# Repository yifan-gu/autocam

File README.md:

Arduino files for my auto-following camera car!

## TODO
- [x] Add dji remote control and receiver
- [x] <s>Add PID encoder</s> Add a web page for parameters
- [x] Add BLE central for the anchor
- [x] Read joystick values for the remote controller
- [x] Read mode switch button for remote controller
- [x] Add state indicator in the web UI
- [x] Add LED state indicators
- [x] Add battery state LED (tag, remote)
- [x] Add LED logic for tag
- [x] Add lock mode (remote)
- [x] Combine tag and remote
  - [x] Add tag selector (sensor, remote)
- [x] Control the BLE data rate
- [x] Fix UWB Anchor naming, fix AutocamController naming
- [x] Add PCB boards
  - [x] Sensor
  - [x] Verify LED resistor values
  - [x] Verify IO0/IO1 port on the ESP32 UWB is usable 
  - [x] Tag
  - [x] Server
  - [x] Remote
- [x] Smooth the distance measurement.
- [x] Added a different mode (follow).
- [x] Added gimbal recenter and camera recording.
- [x] Assemble together
- [x] Design and make the enclosure
- [ ] Calibrate the UWB tag and anchor
- [ ] Measure battery voltage.
- [ ] (optimize) Store settings in external storage (SD card)
- [x] (optimize) Refactor the server code with a state machine, (Almost a state machine now).
- [ ] (optimize) Refactor the sensor LED control with LED controller
- [ ] (optimize) Reorganize shared code into libraries, add external dependencies 

- [x] heartbeat for the remote controller.
- [ ] <s> Nice to have, detect active track failure</s> Turns out there's no API support for that
- [x] Smart Phone APP for the remote (BLE version).

## KNOWN ISSUES
- [ ] Webserver stabability.
- [x] Steering thread issue (Do not steer before throttle is applied)
- [x] BLE connection issue
- [ ] ESC init issue

<s>- [x] Start/stop recording issue</s> Not actually an issue—I plugged the USB-C cable into the wrong gimbal port. However, since the camera drains the gimbal’s battery, I still remove the cable to conserve power.

- [x] Every time the remote buttons are pressed, send values to the server.

## 🚗 Simulator

👉 [Run the Simulator](https://yifan-gu.github.io/autocam/simulator.html)

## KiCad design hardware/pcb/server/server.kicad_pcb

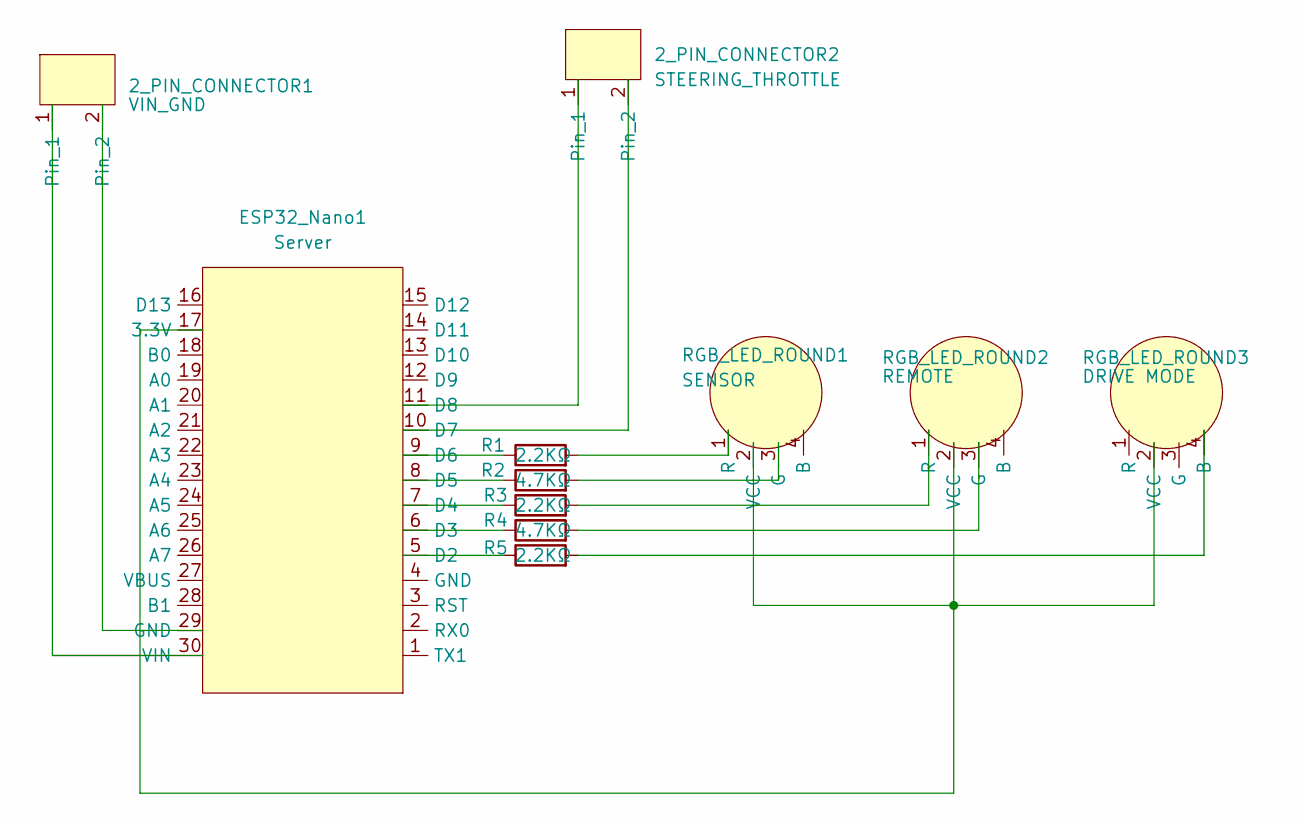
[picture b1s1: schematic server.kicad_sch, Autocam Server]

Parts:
2_PIN_CONNECTOR1: VIN_GND; 2-PIN Connector
2_PIN_CONNECTOR2: STEERING_THROTTLE; 2-PIN Connector
ESP32_Nano1: Server; Arduino ESP32 Nano
R1, R3, R5: 2.2KΩ; Simple Resistor
R2, R4: 4.7KΩ; Simple Resistor
RGB_LED_ROUND1: SENSOR; Anode RGB LED (Round)
RGB_LED_ROUND2: REMOTE; Anode RGB LED (Round)
RGB_LED_ROUND3: DRIVE MODE; Anode RGB LED (Round)

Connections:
unnamed: 2_PIN_CONNECTOR1.1, ESP32_Nano1.30 (VIN)
unnamed: 2_PIN_CONNECTOR1.2, ESP32_Nano1.29 (GND)
unnamed: 2_PIN_CONNECTOR2.1, ESP32_Nano1.11 (D8)
unnamed: 2_PIN_CONNECTOR2.2, ESP32_Nano1.10 (D7)
unnamed: ESP32_Nano1.17 (3.3V), RGB_LED_ROUND1.2 (VCC), RGB_LED_ROUND2.2 (VCC), RGB_LED_ROUND3.2 (VCC)
unnamed: ESP32_Nano1.5 (D2), R5.1
unnamed: ESP32_Nano1.6 (D3), R4.1
unnamed: ESP32_Nano1.7 (D4), R3.1
unnamed: ESP32_Nano1.8 (D5), R2.1
unnamed: ESP32_Nano1.9 (D6), R1.1
unnamed: R2.2, RGB_LED_ROUND1.3 (G)
unnamed: R1.2, RGB_LED_ROUND1.1 (R)
unnamed: R4.2, RGB_LED_ROUND2.3 (G)
unnamed: R3.2, RGB_LED_ROUND2.1 (R)
unnamed: R5.2, RGB_LED_ROUND3.4 (B)

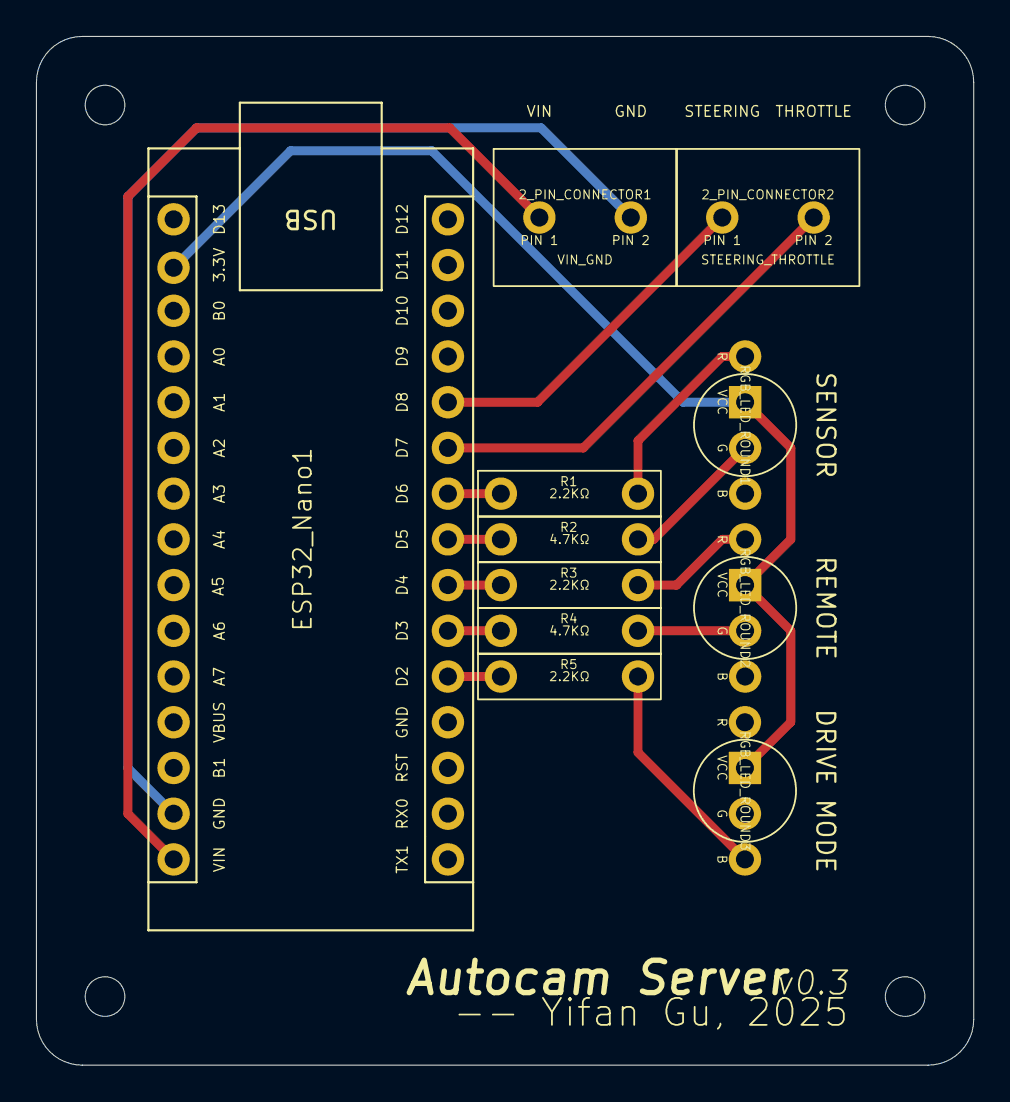
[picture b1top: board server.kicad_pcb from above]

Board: 2 copper layers, 52.1 x 57.2 mm, 11 parts (0 on the bottom side), 15 nets.

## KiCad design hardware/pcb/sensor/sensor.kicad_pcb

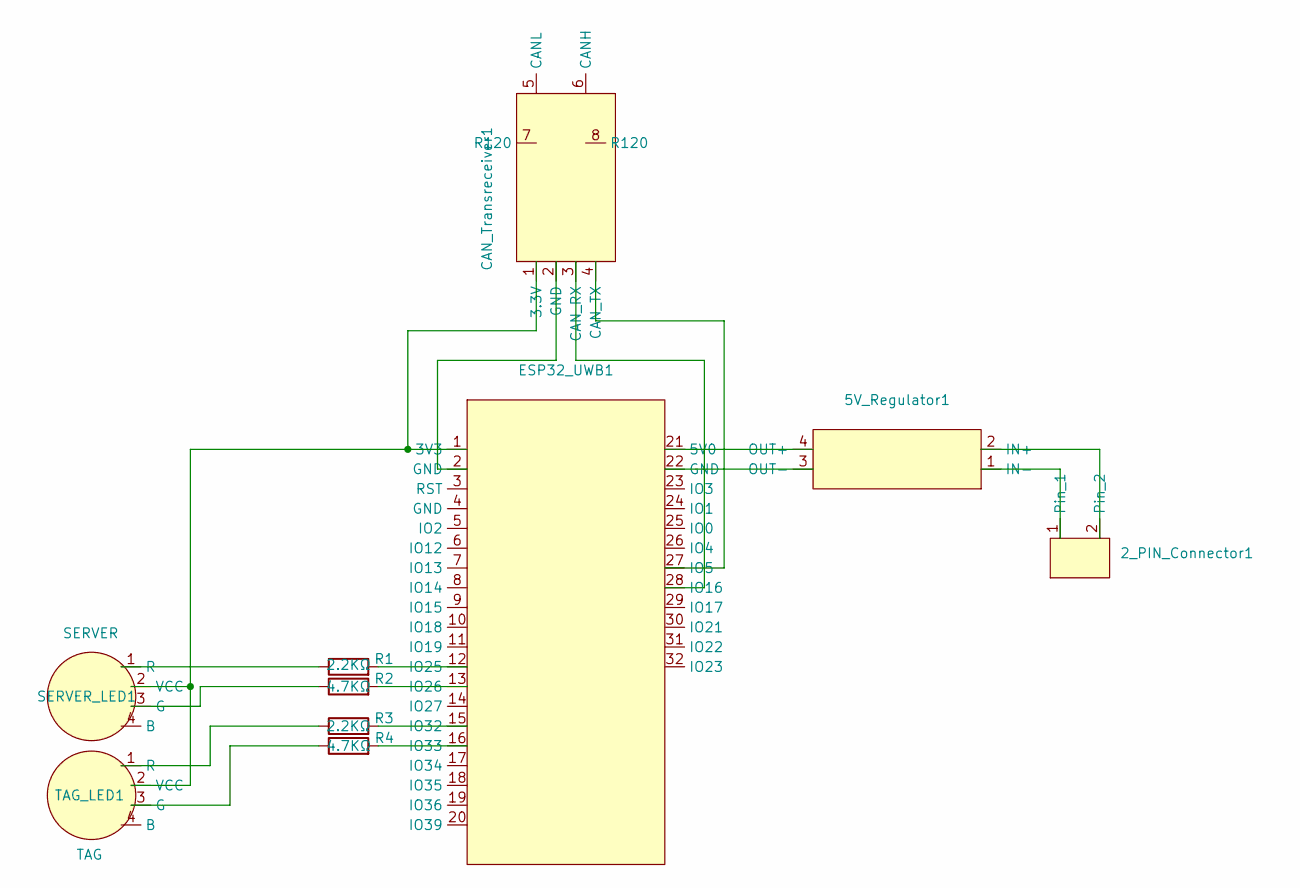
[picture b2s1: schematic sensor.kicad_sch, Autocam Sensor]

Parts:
2_PIN_Connector1: 2-PIN Connector
5V_Regulator1: MP1584EN 5V Regulator
CAN_Transreceiver1: Waveshare CAN Transreceiver
ESP32_UWB1: Makersfab ESP32 UWB
R1, R3: 2.2KΩ; Simple Resistor
R2, R4: 4.7KΩ; Simple Resistor
SERVER_LED1: SERVER; Anode RGB LED (Round)
TAG_LED1: TAG; Anode RGB LED (Round)

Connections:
unnamed: 2_PIN_Connector1.1, 5V_Regulator1.1 (IN-)
unnamed: 2_PIN_Connector1.2, 5V_Regulator1.2 (IN+)
unnamed: 5V_Regulator1.4 (OUT+), ESP32_UWB1.21 (5V0)
unnamed: 5V_Regulator1.3 (OUT-), ESP32_UWB1.22 (GND)
unnamed: CAN_Transreceiver1.1 (3.3V), ESP32_UWB1.1 (3V3), SERVER_LED1.2 (VCC), TAG_LED1.2 (VCC)
unnamed: CAN_Transreceiver1.3 (CAN_RX), ESP32_UWB1.28 (IO16)
unnamed: CAN_Transreceiver1.4 (CAN_TX), ESP32_UWB1.27 (IO5)
unnamed: CAN_Transreceiver1.2 (GND), ESP32_UWB1.2 (GND)
unnamed: ESP32_UWB1.12 (IO25), R1.2
unnamed: ESP32_UWB1.13 (IO26), R2.2
unnamed: ESP32_UWB1.15 (IO32), R3.2
unnamed: ESP32_UWB1.16 (IO33), R4.2
unnamed: R2.1, SERVER_LED1.3 (G)
unnamed: R1.1, SERVER_LED1.1 (R)
unnamed: R4.1, TAG_LED1.3 (G)
unnamed: R3.1, TAG_LED1.1 (R)

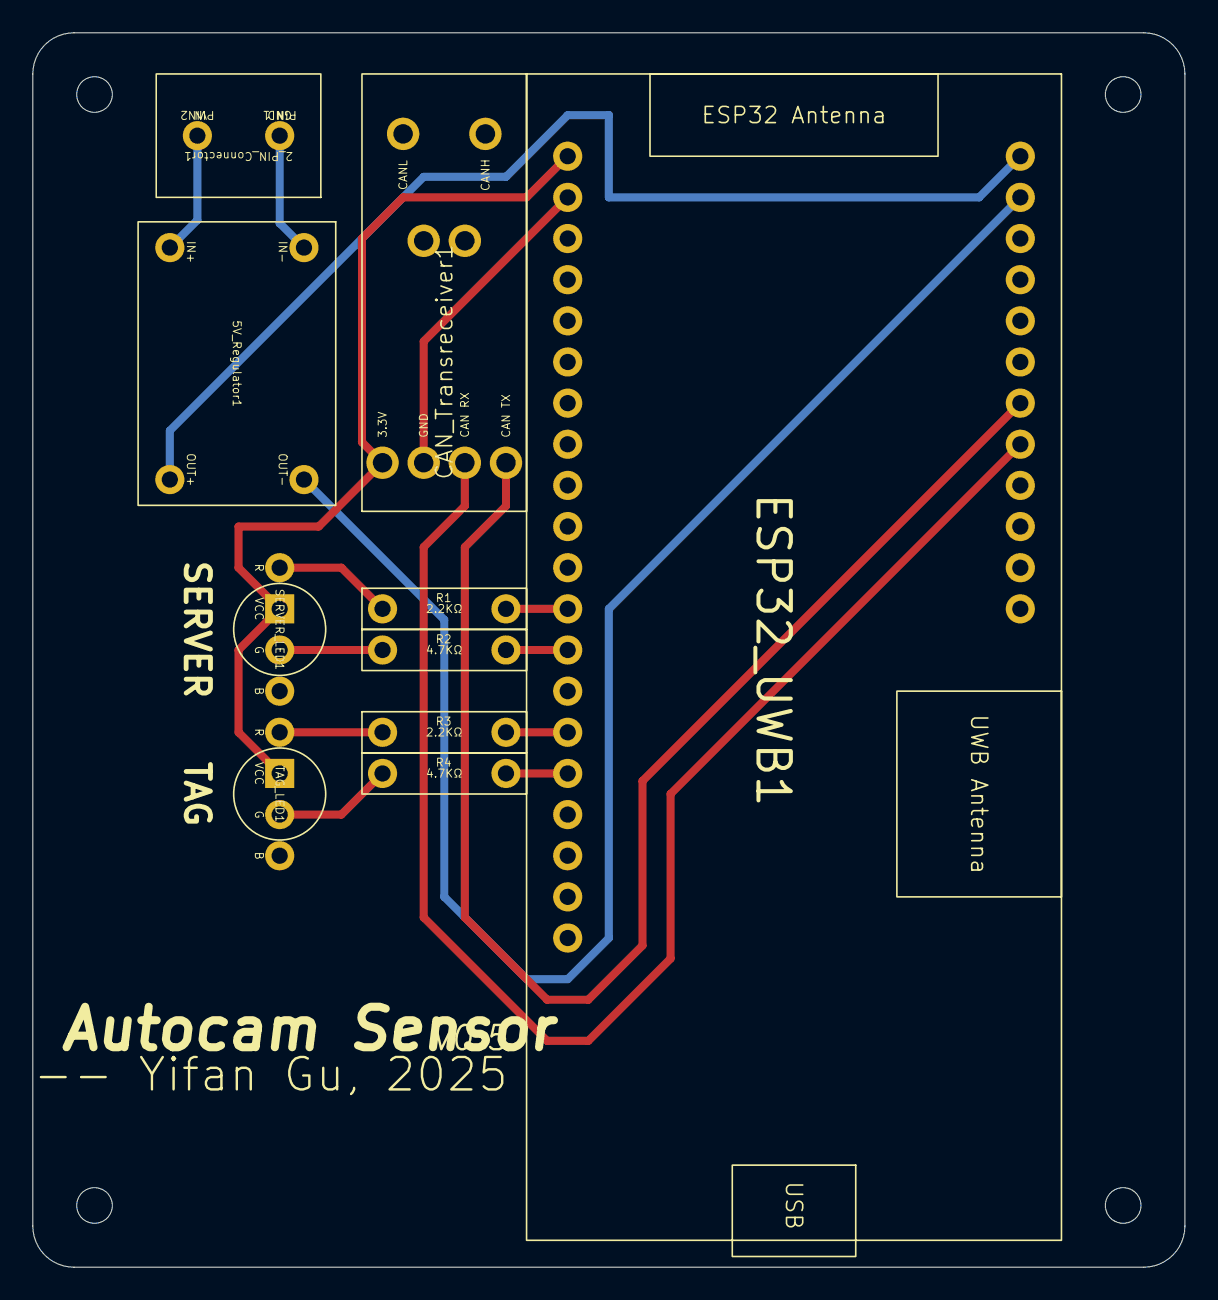
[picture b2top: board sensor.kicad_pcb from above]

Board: 2 copper layers, 71.1 x 76.2 mm, 10 parts (0 on the bottom side), 16 nets.

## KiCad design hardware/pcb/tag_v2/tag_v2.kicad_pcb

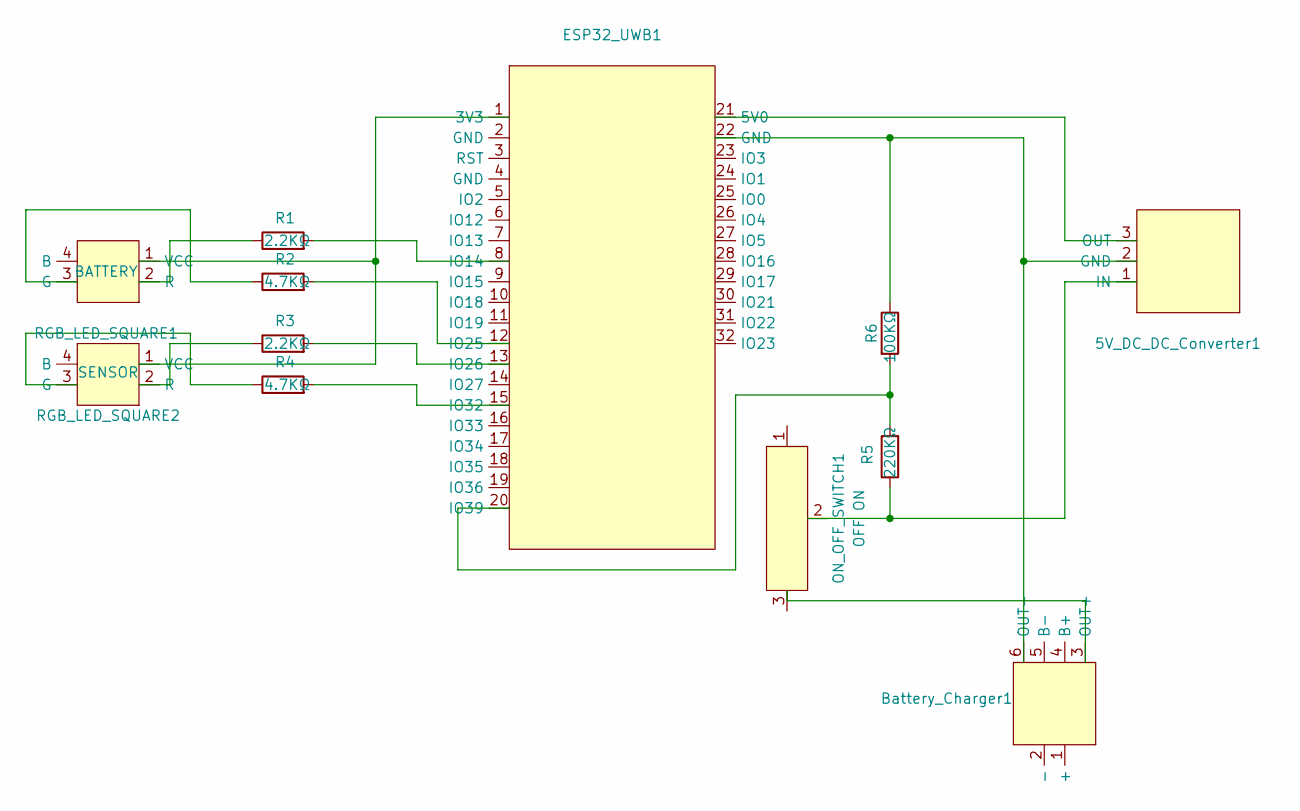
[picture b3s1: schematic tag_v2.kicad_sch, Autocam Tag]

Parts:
5V_DC_DC_Converter1: 5V DC-DC Step Up Converter (Square)
Battery_Charger1: USB-C 3.7V Lithium Battery Charger
ESP32_UWB1: Makersfab ESP32 UWB
ON_OFF_SWITCH1: OFF ON; 3-PIN Switch
R1, R3: 2.2KΩ; Simple Resistor
R2, R4: 4.7KΩ; Simple Resistor
R5: 220KΩ; Simple Resistor
R6: 100KΩ; Simple Resistor
RGB_LED_SQUARE1: BATTERY; Anode RGB LED (Square)
RGB_LED_SQUARE2: SENSOR; Anode RGB LED (Square)

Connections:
unnamed: 5V_DC_DC_Converter1.2 (GND), Battery_Charger1.6 (OUT-), ESP32_UWB1.22 (GND), R6.1
unnamed: 5V_DC_DC_Converter1.1 (IN), ON_OFF_SWITCH1.2, R5.1
unnamed: 5V_DC_DC_Converter1.3 (OUT), ESP32_UWB1.21 (5V0)
unnamed: Battery_Charger1.3 (OUT+), ON_OFF_SWITCH1.3
unnamed: ESP32_UWB1.1 (3V3), RGB_LED_SQUARE1.1 (VCC), RGB_LED_SQUARE2.1 (VCC)
unnamed: ESP32_UWB1.8 (IO14), R1.2
unnamed: ESP32_UWB1.12 (IO25), R2.2
unnamed: ESP32_UWB1.13 (IO26), R3.2
unnamed: ESP32_UWB1.15 (IO32), R4.2
unnamed: ESP32_UWB1.20 (IO39), R5.2, R6.2
unnamed: R2.1, RGB_LED_SQUARE1.3 (G)
unnamed: R1.1, RGB_LED_SQUARE1.2 (R)
unnamed: R4.1, RGB_LED_SQUARE2.3 (G)
unnamed: R3.1, RGB_LED_SQUARE2.2 (R)

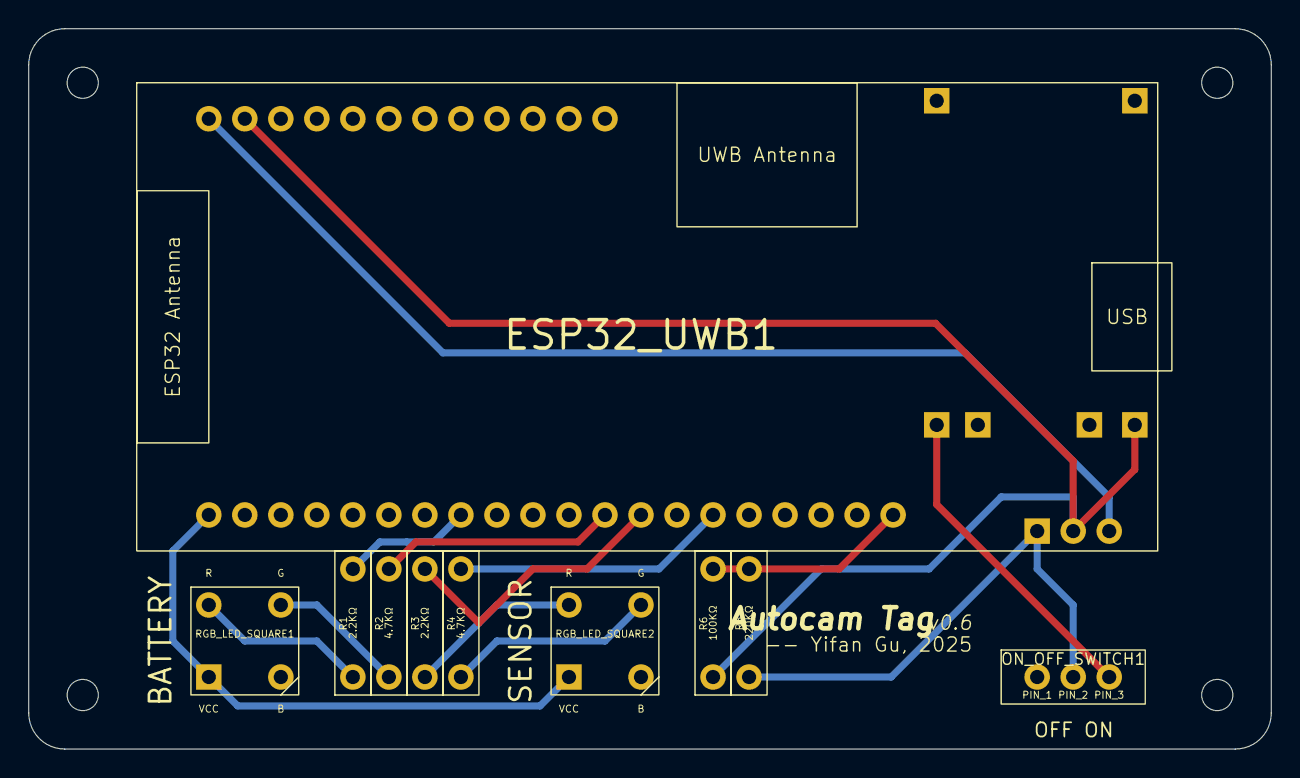
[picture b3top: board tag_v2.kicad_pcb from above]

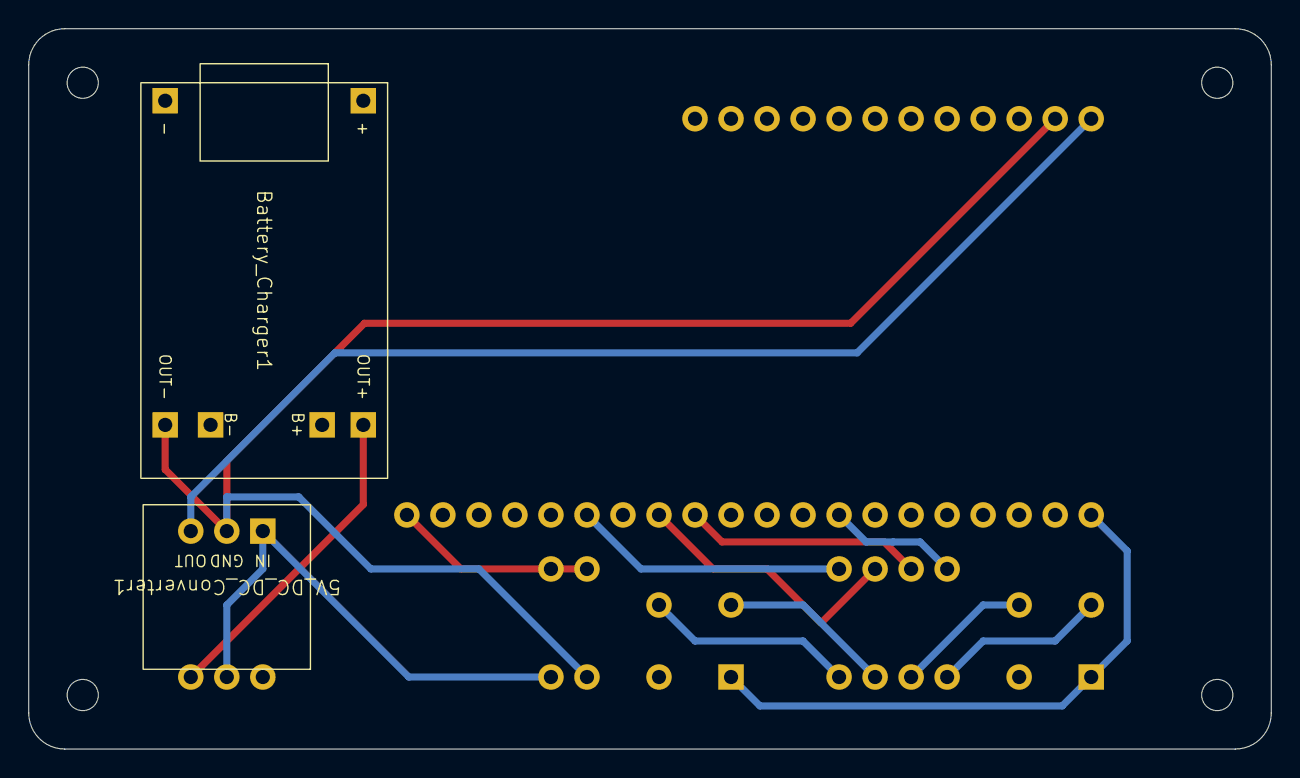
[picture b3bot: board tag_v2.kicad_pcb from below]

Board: 2 copper layers, 87.6 x 50.8 mm, 12 parts (2 on the bottom side), 14 nets.

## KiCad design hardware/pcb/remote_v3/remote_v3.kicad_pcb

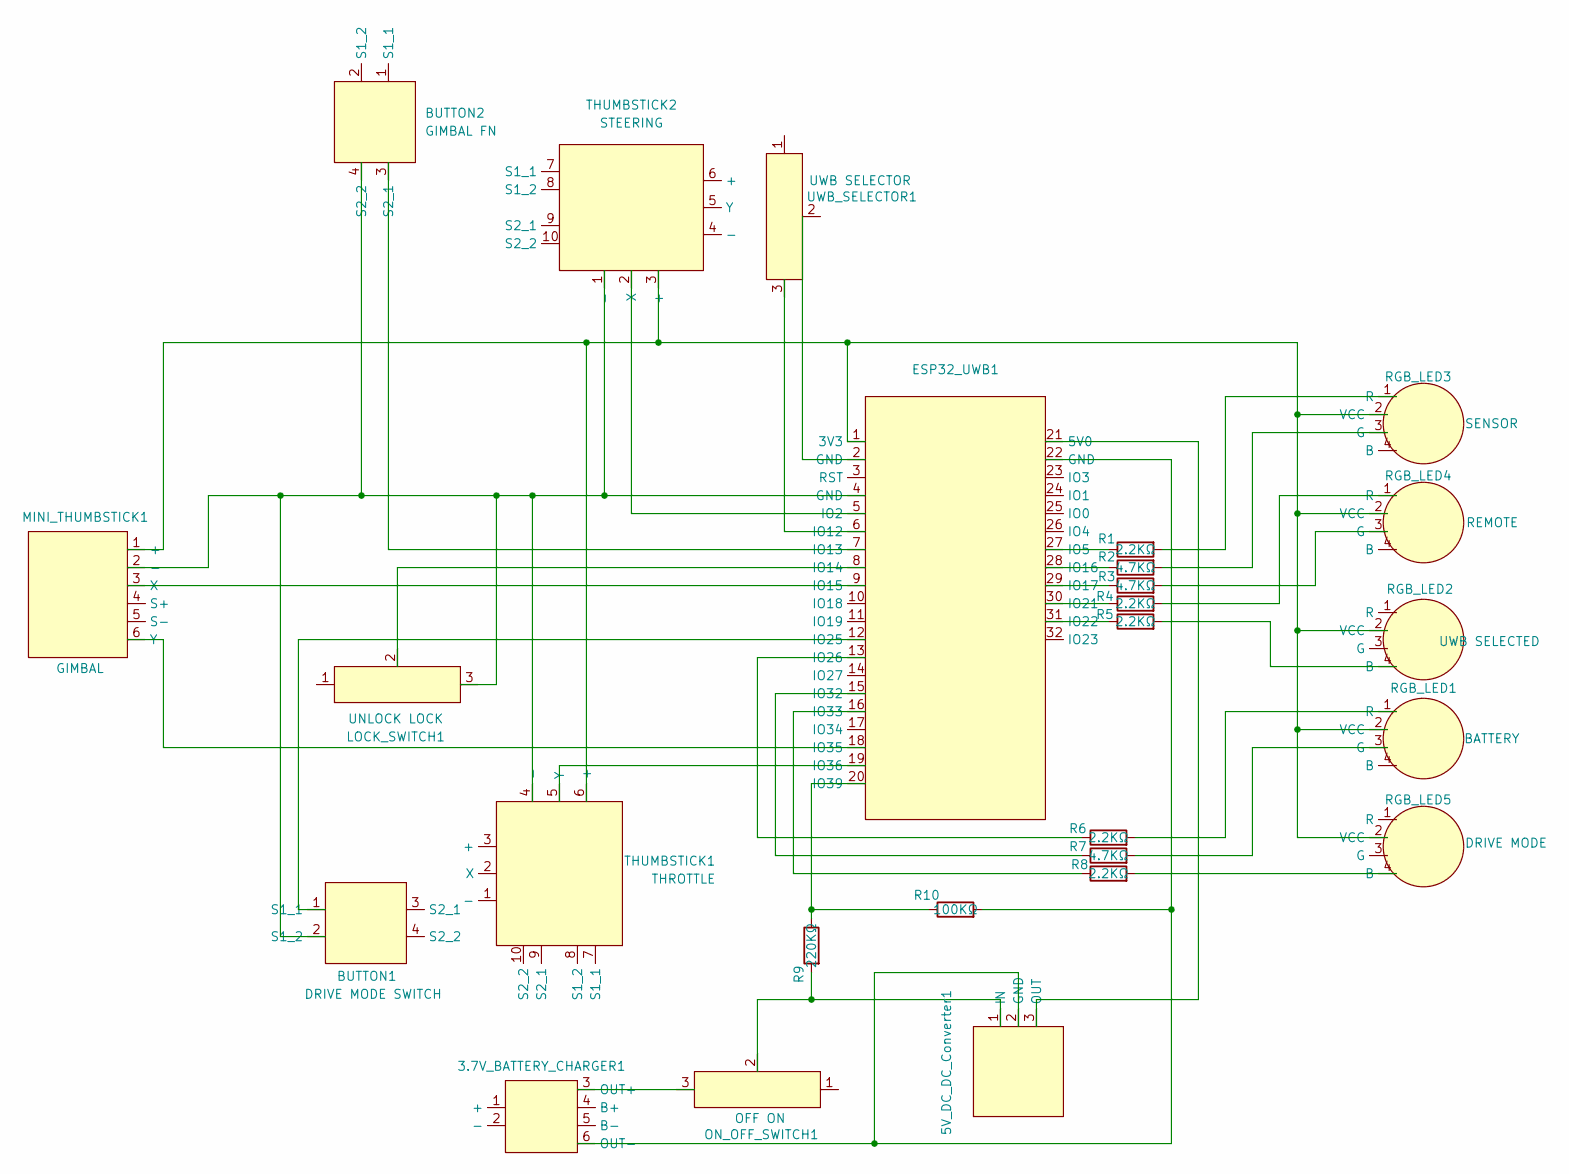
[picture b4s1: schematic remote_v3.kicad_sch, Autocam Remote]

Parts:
3.7V_BATTERY_CHARGER1: USB-C 3.7V Lithium Battery Charger
5V_DC_DC_Converter1: 5V DC-DC Step Up Converter (Square)
BUTTON1: DRIVE MODE SWITCH; Tactile Switch Button (Square)
BUTTON2: GIMBAL FN; Tactile Switch Button (Square)
ESP32_UWB1: Makersfab ESP32 UWB
LOCK_SWITCH1: UNLOCK LOCK; 3-PIN Switch
MINI_THUMBSTICK1: GIMBAL; Mini Analog Joystick
ON_OFF_SWITCH1: OFF ON; 3-PIN Switch
R1, R4, R5, R6, R8: 2.2KΩ; Simple Resistor
R2, R3, R7: 4.7KΩ; Simple Resistor
R9: 220KΩ; Simple Resistor
R10: 100KΩ; Simple Resistor
RGB_LED1: BATTERY; Anode RGB LED (Round)
RGB_LED2: UWB SELECTED; Anode RGB LED (Round)
RGB_LED3: SENSOR; Anode RGB LED (Round)
RGB_LED4: REMOTE; Anode RGB LED (Round)
RGB_LED5: DRIVE MODE; Anode RGB LED (Round)
THUMBSTICK1: THROTTLE; X-Box Style Thumbstick
THUMBSTICK2: STEERING; X-Box Style Thumbstick
UWB_SELECTOR1: UWB SELECTOR; 3-PIN Switch

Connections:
unnamed: 3.7V_BATTERY_CHARGER1.3 (OUT+), ON_OFF_SWITCH1.3
unnamed: 3.7V_BATTERY_CHARGER1.6 (OUT-), 5V_DC_DC_Converter1.2 (GND), ESP32_UWB1.22 (GND), R10.2
unnamed: 5V_DC_DC_Converter1.1 (IN), ON_OFF_SWITCH1.2, R9.2
unnamed: 5V_DC_DC_Converter1.3 (OUT), ESP32_UWB1.21 (5V0)
unnamed: BUTTON1.1 (S1), ESP32_UWB1.12 (IO25)
unnamed: BUTTON1.2 (S1), BUTTON2.4 (S2_2), ESP32_UWB1.4 (GND), LOCK_SWITCH1.3, MINI_THUMBSTICK1.2 (-), THUMBSTICK1.4 (-), THUMBSTICK2.1 (-)
unnamed: BUTTON2.3 (S2_1), ESP32_UWB1.7 (IO13)
unnamed: ESP32_UWB1.1 (3V3), MINI_THUMBSTICK1.1 (+), RGB_LED1.2 (VCC), RGB_LED2.2 (VCC), RGB_LED3.2 (VCC), RGB_LED4.2 (VCC), RGB_LED5.2 (VCC), THUMBSTICK1.6 (+), THUMBSTICK2.3 (+)
unnamed: ESP32_UWB1.2 (GND), UWB_SELECTOR1.2
unnamed: ESP32_UWB1.5 (IO2), THUMBSTICK2.2 (X)
unnamed: ESP32_UWB1.27 (IO5), R1.1
unnamed: ESP32_UWB1.6 (IO12), UWB_SELECTOR1.3
unnamed: ESP32_UWB1.8 (IO14), LOCK_SWITCH1.2
unnamed: ESP32_UWB1.9 (IO15), MINI_THUMBSTICK1.3 (X)
unnamed: ESP32_UWB1.28 (IO16), R2.1
unnamed: ESP32_UWB1.29 (IO17), R3.1
unnamed: ESP32_UWB1.30 (IO21), R4.1
unnamed: ESP32_UWB1.31 (IO22), R5.1
unnamed: ESP32_UWB1.13 (IO26), R6.1
unnamed: ESP32_UWB1.15 (IO32), R7.1
unnamed: ESP32_UWB1.16 (IO33), R8.1
unnamed: ESP32_UWB1.18 (IO35), MINI_THUMBSTICK1.6 (Y)
unnamed: ESP32_UWB1.19 (IO36), THUMBSTICK1.5 (Y)
unnamed: ESP32_UWB1.20 (IO39), R9.1, R10.1
unnamed: R7.2, RGB_LED1.3 (G)
unnamed: R6.2, RGB_LED1.1 (R)
unnamed: R5.2, RGB_LED2.4 (B)
unnamed: R2.2, RGB_LED3.3 (G)
unnamed: R1.2, RGB_LED3.1 (R)
unnamed: R3.2, RGB_LED4.3 (G)
unnamed: R4.2, RGB_LED4.1 (R)
unnamed: R8.2, RGB_LED5.4 (B)

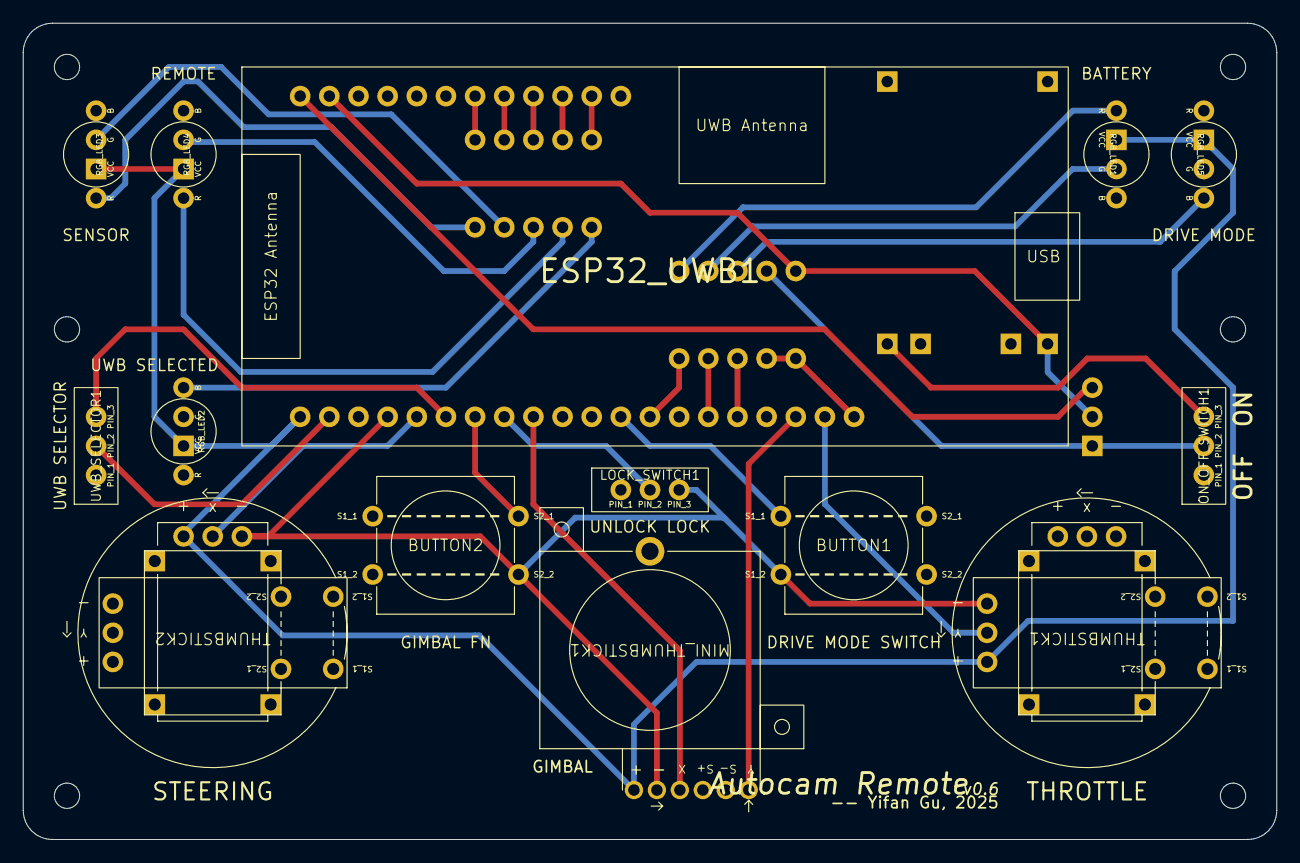
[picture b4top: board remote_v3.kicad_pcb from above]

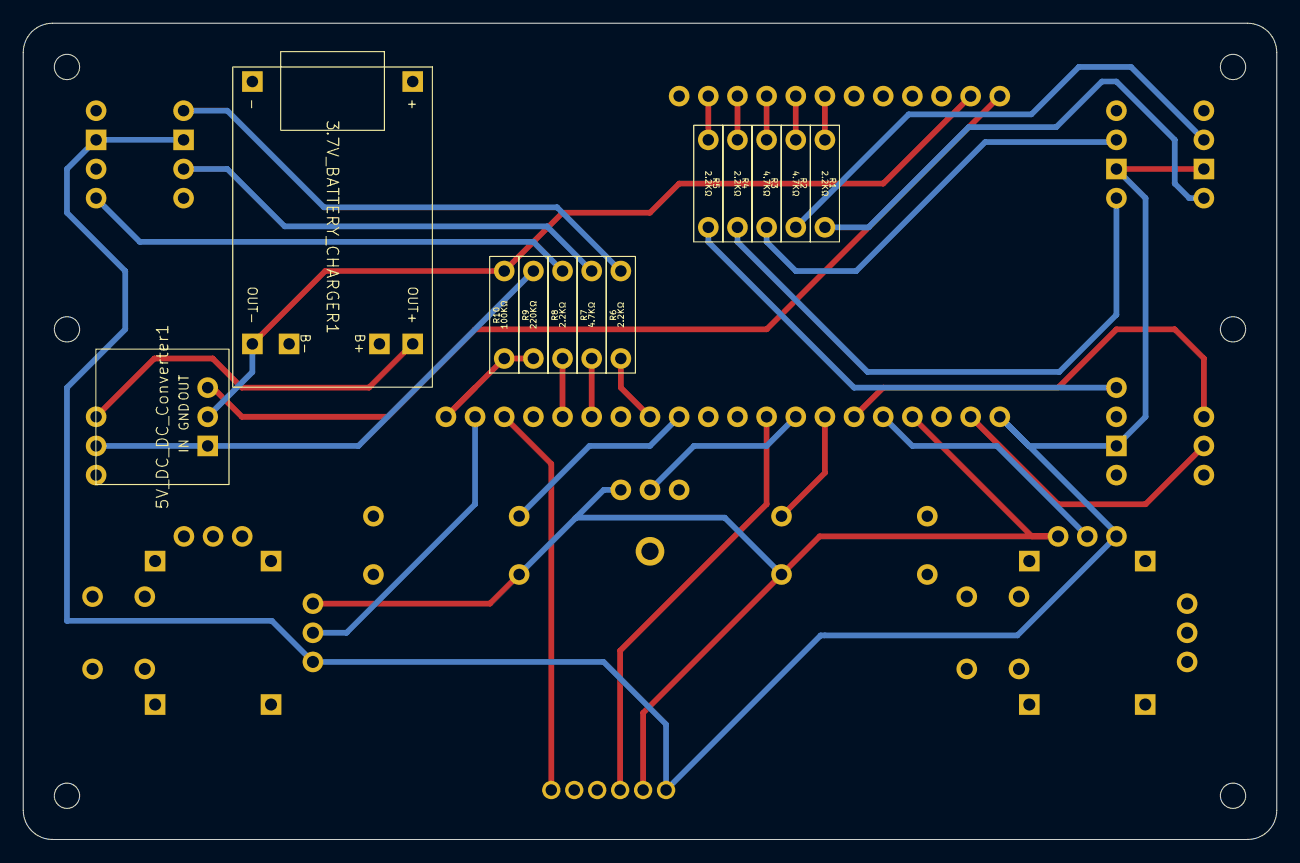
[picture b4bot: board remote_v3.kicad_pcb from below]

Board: 2 copper layers, 109.2 x 71.1 mm, 26 parts (12 on the bottom side), 32 nets.

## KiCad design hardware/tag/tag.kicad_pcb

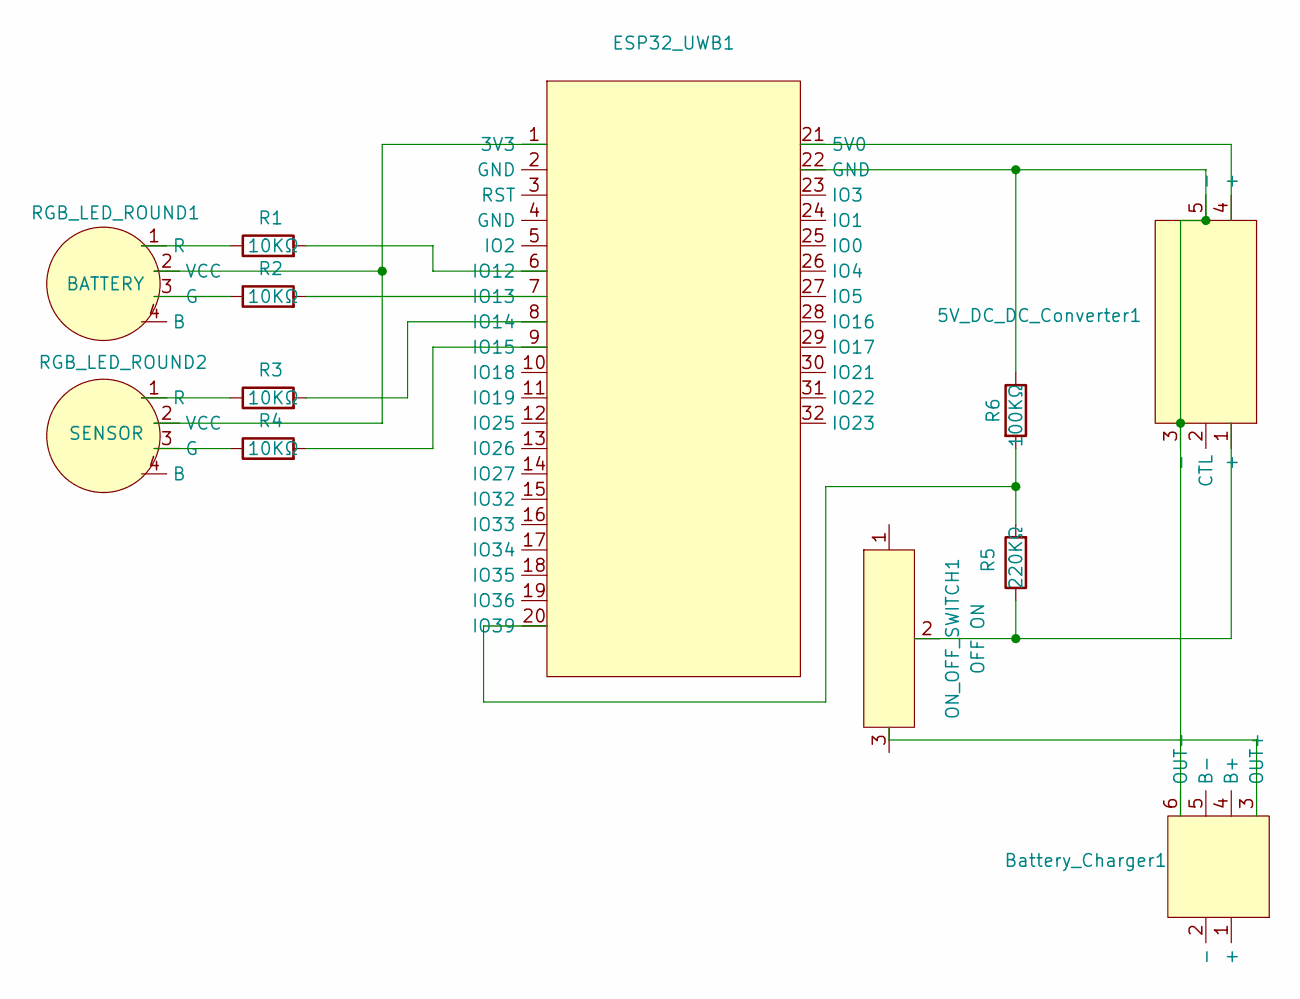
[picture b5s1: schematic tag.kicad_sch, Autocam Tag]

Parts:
5V_DC_DC_Converter1: 5V DC-DC Step Up Converter (Rectangle)
Battery_Charger1: USB-C 3.7V Lithium Battery Charger
ESP32_UWB1: Makersfab ESP32 UWB
ON_OFF_SWITCH1: OFF ON; 3-PIN Switch
R1, R2, R3, R4: 10KΩ; Simple Resistor
R5: 220KΩ; Simple Resistor
R6: 100KΩ; Simple Resistor
RGB_LED_ROUND1: BATTERY; Anode RGB LED (Round)
RGB_LED_ROUND2: SENSOR; Anode RGB LED (Round)

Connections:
unnamed: 5V_DC_DC_Converter1.1 (+), ON_OFF_SWITCH1.2, R5.1
unnamed: Battery_Charger1.3 (OUT+), ON_OFF_SWITCH1.3
unnamed: 5V_DC_DC_Converter1.3 (-), 5V_DC_DC_Converter1.5 (-), Battery_Charger1.6 (OUT-), ESP32_UWB1.22 (GND), R6.1
unnamed: ESP32_UWB1.1 (3V3), RGB_LED_ROUND1.2 (VCC), RGB_LED_ROUND2.2 (VCC)
unnamed: 5V_DC_DC_Converter1.4 (+), ESP32_UWB1.21 (5V0)
unnamed: ESP32_UWB1.6 (IO12), R1.2
unnamed: ESP32_UWB1.7 (IO13), R2.2
unnamed: ESP32_UWB1.8 (IO14), R3.2
unnamed: ESP32_UWB1.9 (IO15), R4.2
unnamed: ESP32_UWB1.20 (IO39), R5.2, R6.2
unnamed: R2.1, RGB_LED_ROUND1.3 (G)
unnamed: R1.1, RGB_LED_ROUND1.1 (R)
unnamed: R4.1, RGB_LED_ROUND2.3 (G)
unnamed: R3.1, RGB_LED_ROUND2.1 (R)

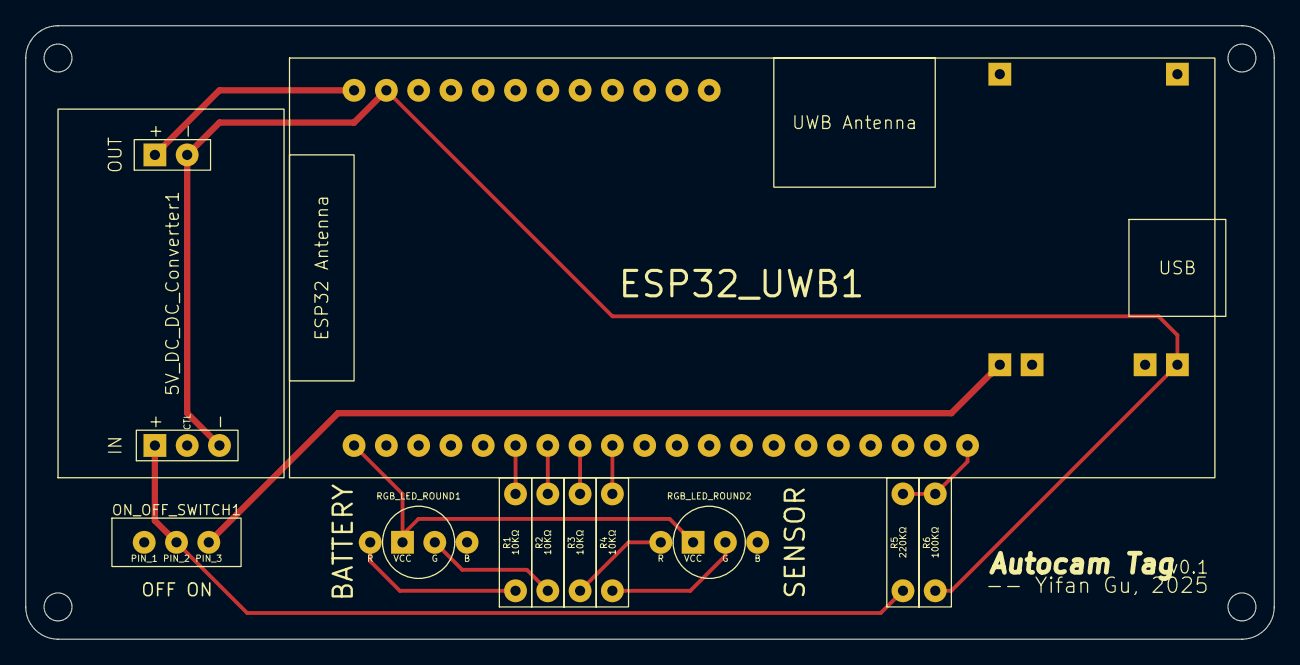
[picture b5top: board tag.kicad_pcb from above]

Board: 2 copper layers, 98.2 x 48.3 mm, 12 parts (1 on the bottom side), 14 nets.
